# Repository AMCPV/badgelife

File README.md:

#badgelife
==========

Contains hardware CAD files for ec0's various badge mods.

Uses the SAO or LSAO conference badge addon ports. Planning on some SAO v1.69bis add-ons soon!

See Also
--------

- [Resources for #badgelife](https://github.com/devec0/badgelife-parts)

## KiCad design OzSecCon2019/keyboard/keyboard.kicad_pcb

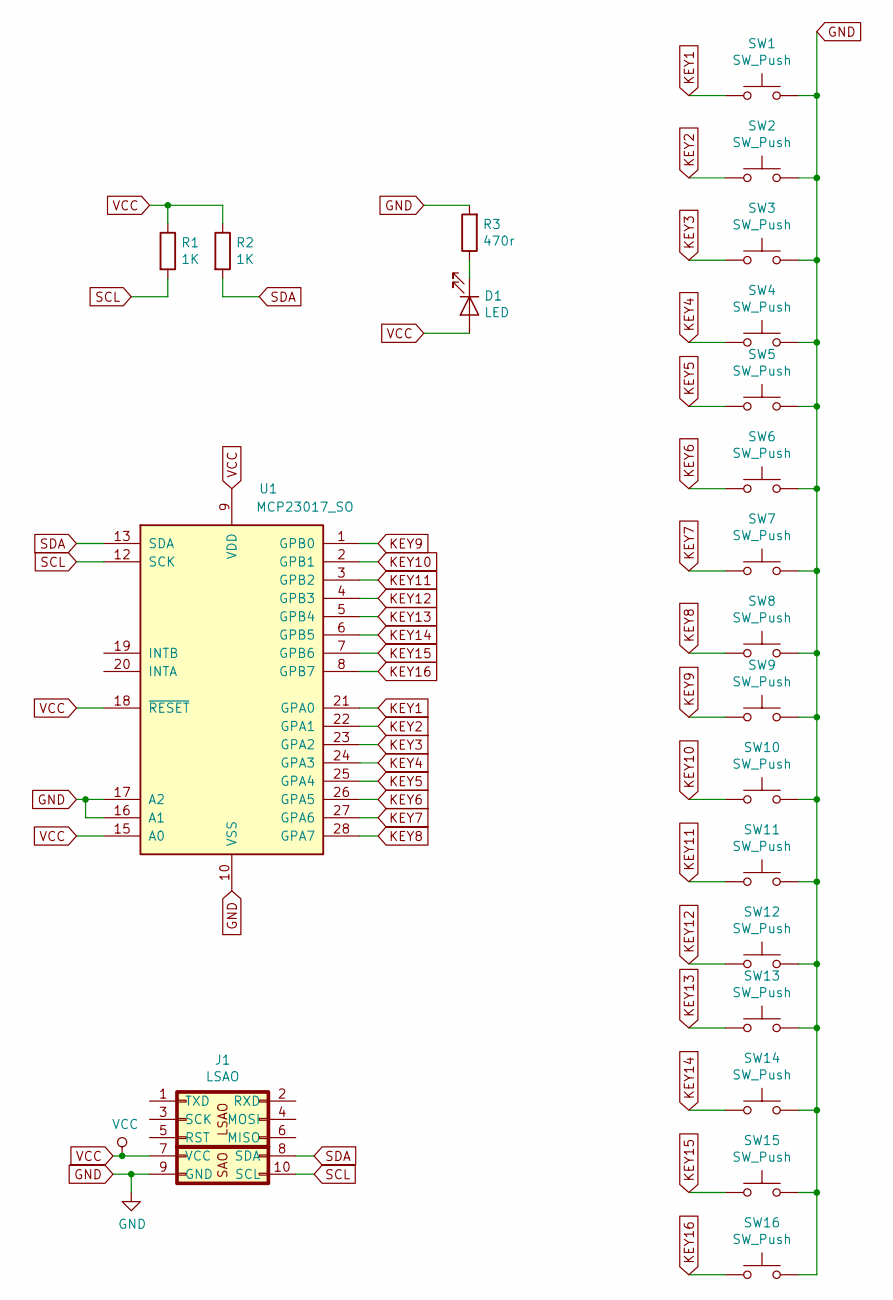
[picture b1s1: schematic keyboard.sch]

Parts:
D1: LED; LED_0805_2012Metric
J1: LSAO; PinSocket_2x05_P2.54mm_Vertical\",
R1, R2: 1K; R_0805_2012Metric
R3: 470r; R_0805_2012Metric
SW1, SW2, SW3, SW4, SW5, SW6, SW7, SW8, SW9, SW10, SW11, SW12, SW13, SW14, SW15, SW16: SW_Push; SW_Cherry_MX1A_1.00u_PCB
U1: MCP23017_SO; SOIC-28W_7.5x17.9mm_P1.27mm

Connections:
GND: J1.9 (GND), R3.2, SW1.2, SW2.2, SW3.2, SW4.2, SW5.2, SW6.2, SW7.2, SW8.2, SW9.2, SW10.2, SW11.2, SW12.2, SW13.2, SW14.2, SW15.2, SW16.2, U1.10 (VSS), U1.16 (A1), U1.17 (A2)
KEY1: SW1.1, U1.21 (GPA0)
KEY2: SW2.1, U1.22 (GPA1)
KEY3: SW3.1, U1.23 (GPA2)
KEY4: SW4.1, U1.24 (GPA3)
KEY5: SW5.1, U1.25 (GPA4)
KEY6: SW6.1, U1.26 (GPA5)
KEY7: SW7.1, U1.27 (GPA6)
KEY8: SW8.1, U1.28 (GPA7)
KEY9: SW9.1, U1.1 (GPB0)
KEY10: SW10.1, U1.2 (GPB1)
KEY11: SW11.1, U1.3 (GPB2)
KEY12: SW12.1, U1.4 (GPB3)
KEY13: SW13.1, U1.5 (GPB4)
KEY14: SW14.1, U1.6 (GPB5)
KEY15: SW15.1, U1.7 (GPB6)
KEY16: SW16.1, U1.8 (GPB7)
unnamed: D1.1 (K), R3.1
SCL: J1.10 (SCL), R1.2, U1.12 (SCK)
SDA: J1.8 (SDA), R2.2, U1.13 (SDA)
VCC: D1.2 (A), J1.7 (VCC), R1.1, R2.1, U1.9 (VDD), U1.15 (A0), U1.18 (~RESET~)

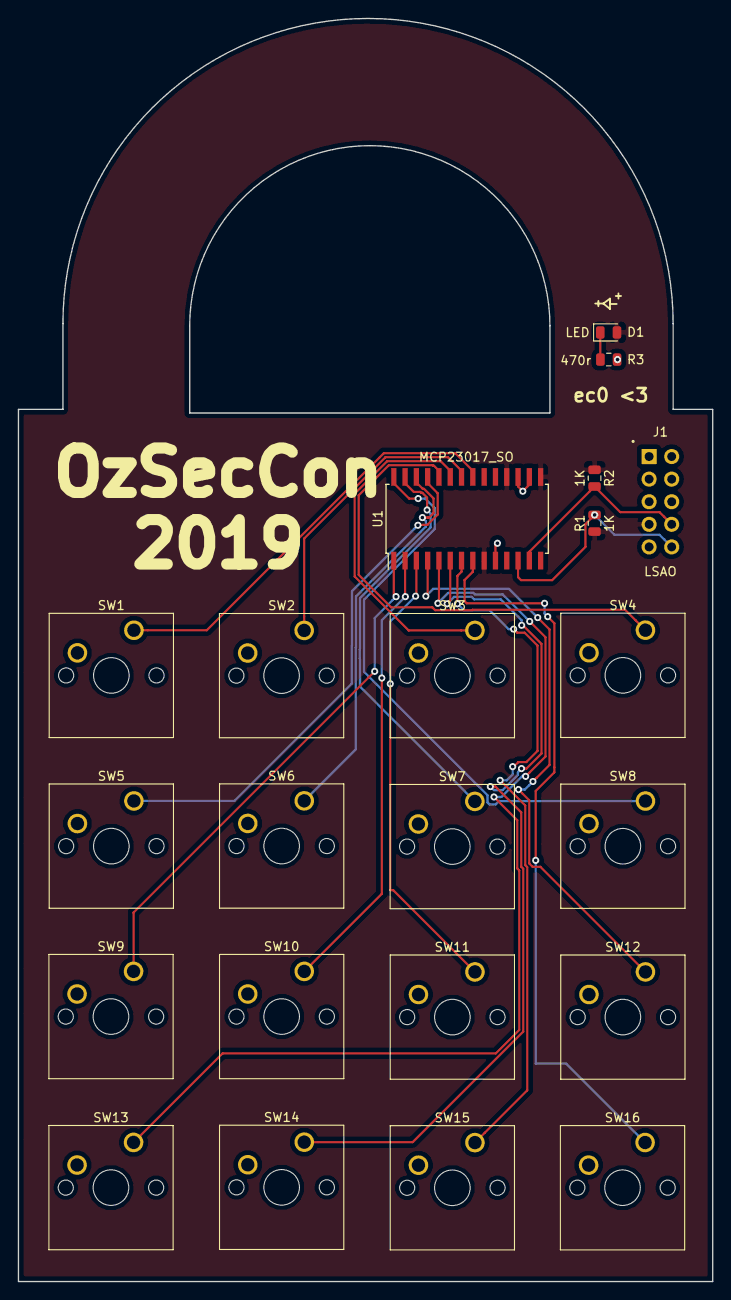
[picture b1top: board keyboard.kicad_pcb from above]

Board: 2 copper layers, 78.0 x 142.0 mm, 22 parts (1 on the bottom side), 21 nets.

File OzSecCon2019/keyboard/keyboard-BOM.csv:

"Id";"Designator";"Package";"Quantity";"Designation";"Supplier and ref";
1;"J1";"PinSocket_2x05_P2.54mm_Vertical";1;"LSAO";;;
2;"R1,R2";"R_0805_2012Metric";2;"1K";;;
3;"SW1,SW2,SW3,SW4,SW5,SW6,SW7,SW8,SW9,SW10,SW11,SW12,SW13,SW14,SW15,SW16";"SW_Cherry_MX1A_1.00u_PCB";16;"SW_Push";;;
4;"U1";"SOIC-28W_7.5x17.9mm_P1.27mm";1;"MCP23017_SO";;;
5;"R3";"R_0805_2012Metric";1;"470r";;;
6;"D1";"LED_0805_2012Metric";1;"LED";;;

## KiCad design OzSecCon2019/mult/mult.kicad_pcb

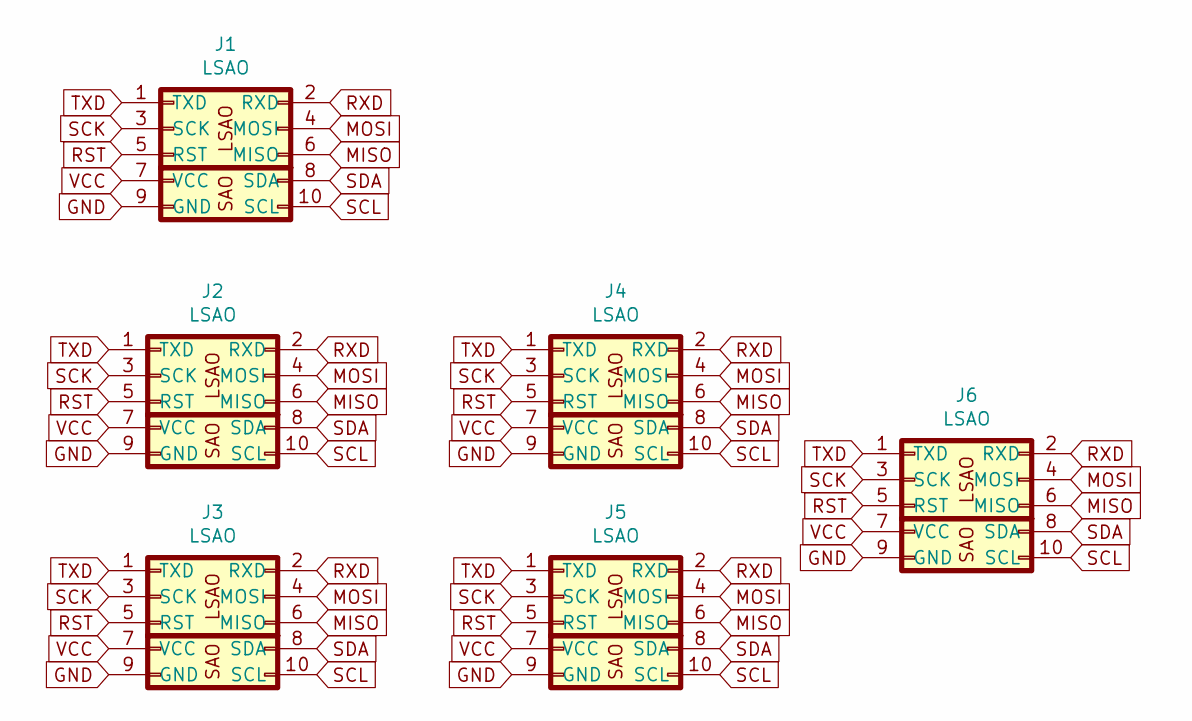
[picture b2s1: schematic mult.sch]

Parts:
J1: LSAO; PinSocket_2x05_P2.54mm_Vertical
J2, J3, J4, J5, J6: LSAO; PinHeader_2x05_P2.54mm_Vertical

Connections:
GND: J1.9 (GND), J2.9 (GND), J3.9 (GND), J4.9 (GND), J5.9 (GND), J6.9 (GND)
MISO: J1.6 (MISO), J2.6 (MISO), J3.6 (MISO), J4.6 (MISO), J5.6 (MISO), J6.6 (MISO)
MOSI: J1.4 (MOSI), J2.4 (MOSI), J3.4 (MOSI), J4.4 (MOSI), J5.4 (MOSI), J6.4 (MOSI)
RST: J1.5 (RST), J2.5 (RST), J3.5 (RST), J4.5 (RST), J5.5 (RST), J6.5 (RST)
RXD: J1.2 (RXD), J2.2 (RXD), J3.2 (RXD), J4.2 (RXD), J5.2 (RXD), J6.2 (RXD)
SCK: J1.3 (SCK), J2.3 (SCK), J3.3 (SCK), J4.3 (SCK), J5.3 (SCK), J6.3 (SCK)
SCL: J1.10 (SCL), J2.10 (SCL), J3.10 (SCL), J4.10 (SCL), J5.10 (SCL), J6.10 (SCL)
SDA: J1.8 (SDA), J2.8 (SDA), J3.8 (SDA), J4.8 (SDA), J5.8 (SDA), J6.8 (SDA)
TXD: J1.1 (TXD), J2.1 (TXD), J3.1 (TXD), J4.1 (TXD), J5.1 (TXD), J6.1 (TXD)
VCC: J1.7 (VCC), J2.7 (VCC), J3.7 (VCC), J4.7 (VCC), J5.7 (VCC), J6.7 (VCC)

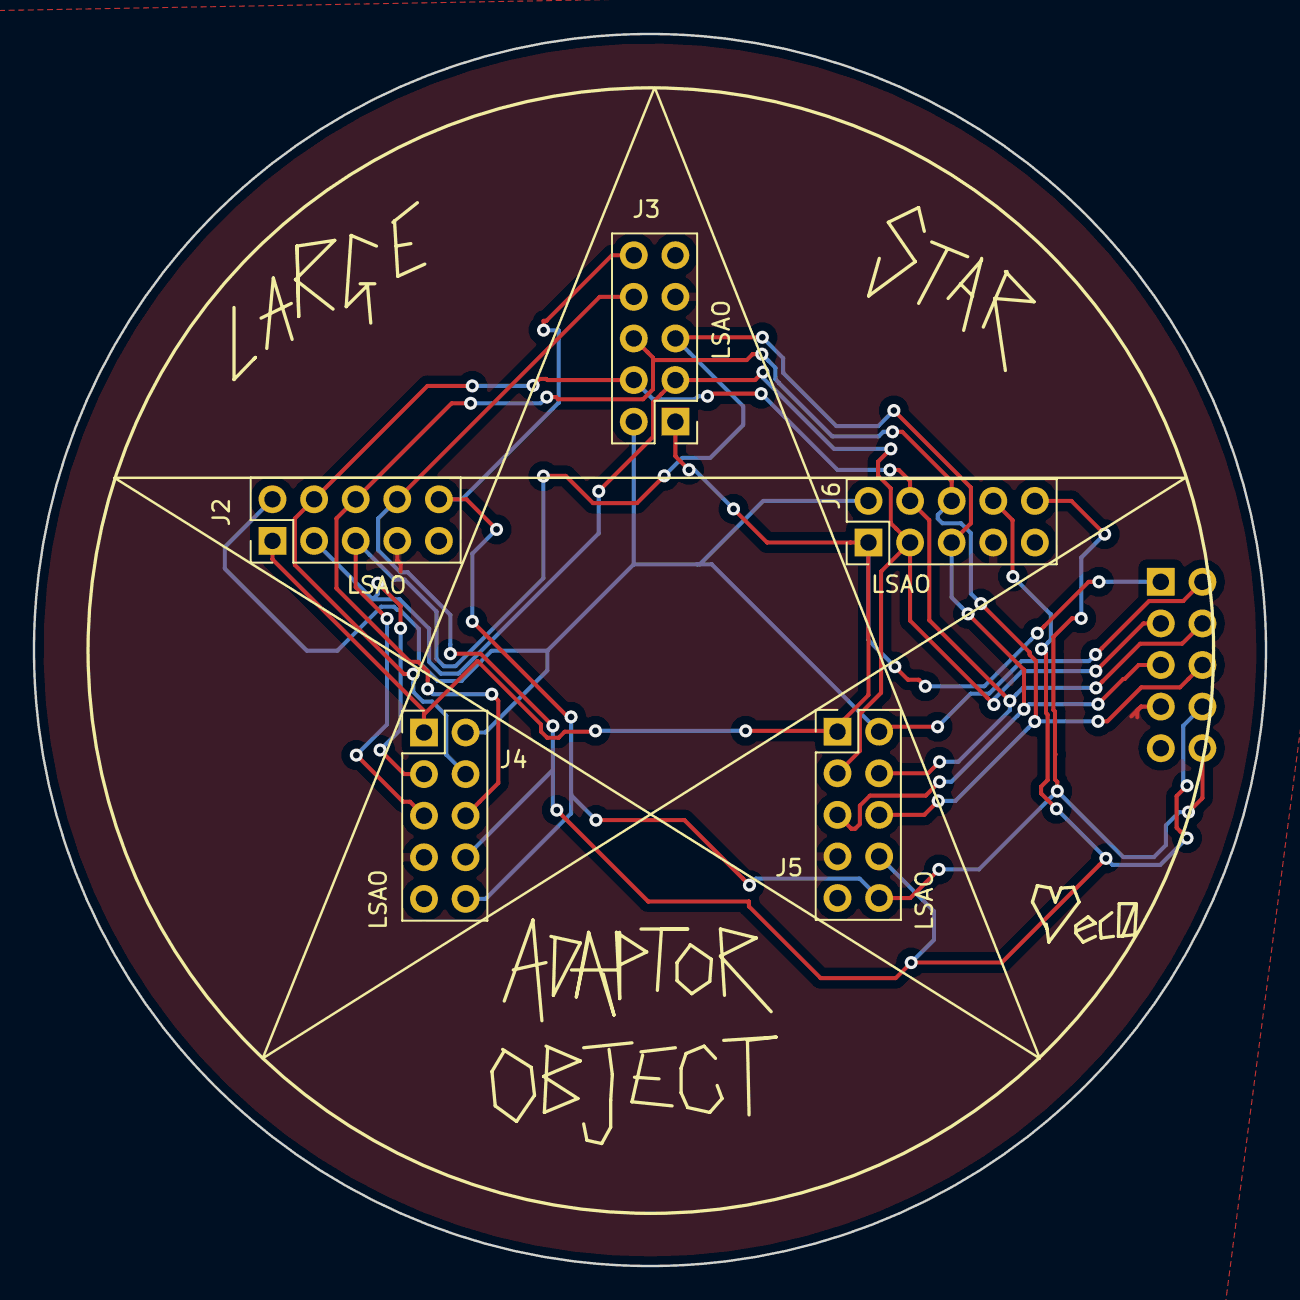
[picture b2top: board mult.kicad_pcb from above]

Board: 2 copper layers, 75.2 x 75.2 mm, 6 parts (1 on the bottom side), 10 nets.

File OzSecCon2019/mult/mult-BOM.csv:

"Id";"Designator";"Package";"Quantity";"Designation";"Supplier and ref";
1;"J1";"PinSocket_2x05_P2.54mm_Vertical";1;"LSAO";;;
2;"J2,J3,J4,J5,J6";"PinHeader_2x05_P2.54mm_Vertical";5;"LSAO";;;

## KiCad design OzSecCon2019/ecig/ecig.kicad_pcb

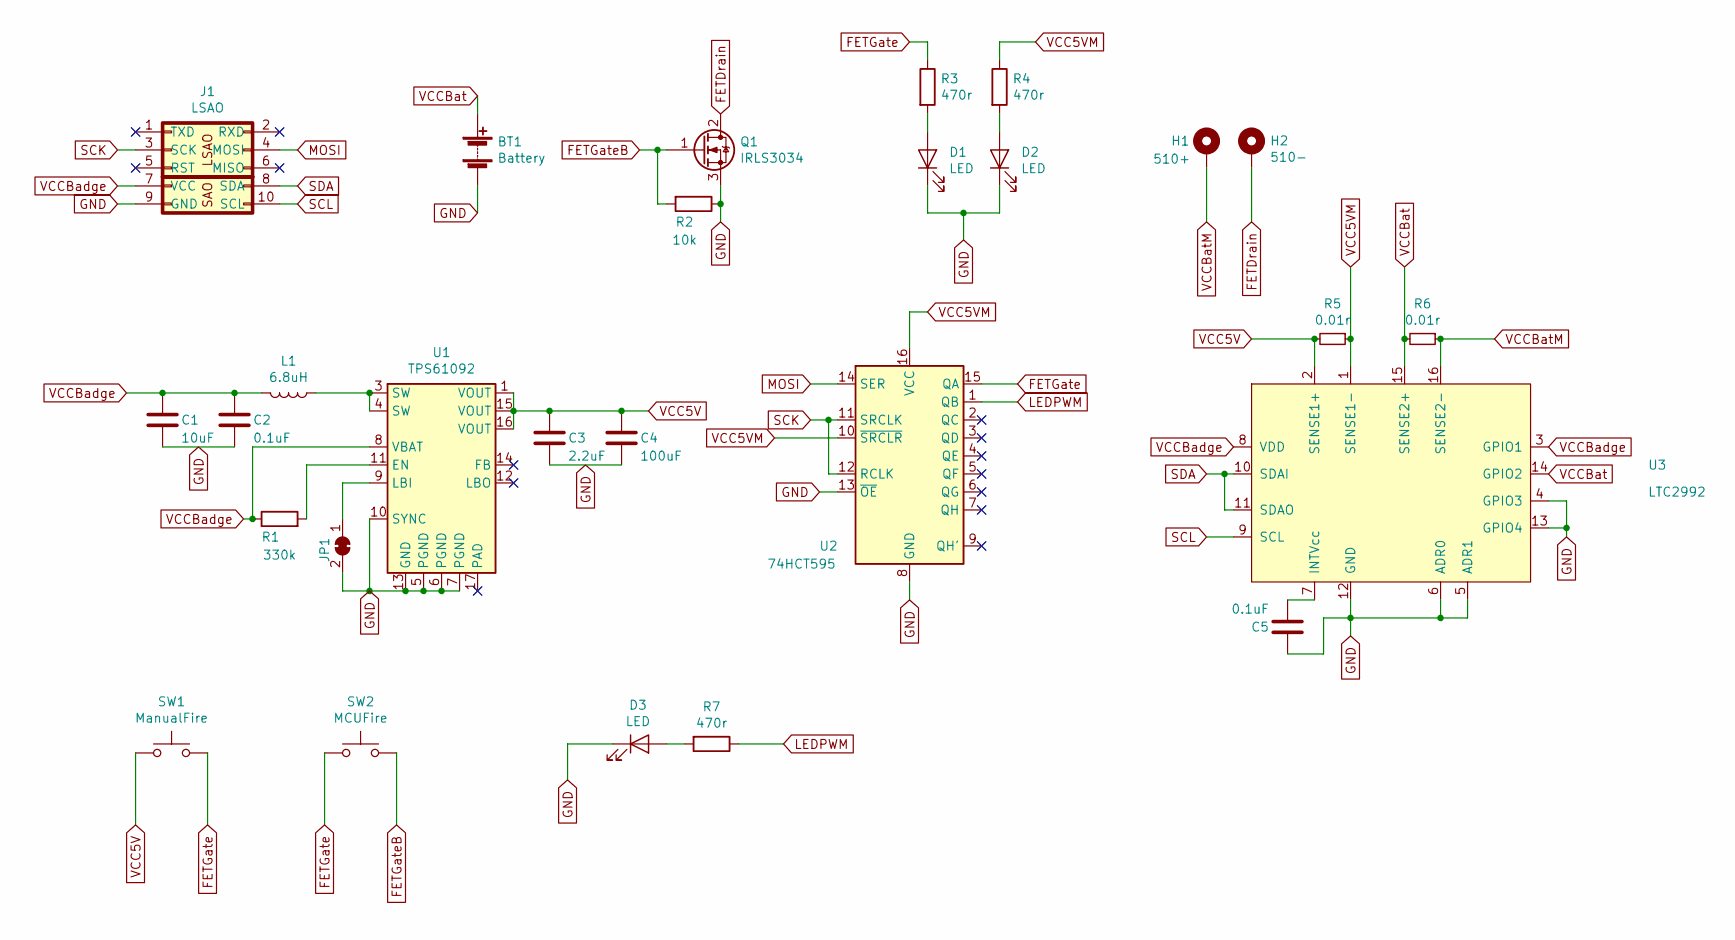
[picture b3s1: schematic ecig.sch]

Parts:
BT1: Battery; BatteryHolder_Keystone_1042_1x18650
C1: 10uF; C_0805_2012Metric
C2, C5: 0.1uF; C_0805_2012Metric
C3: 2.2uF; C_0805_2012Metric
C4: 100uF; C_0805_2012Metric
D1, D2, D3: LED; LED_0805_2012Metric
H1: 510+; Pin_D1.3mm_L11.3mm_W2.8mm_Flat
H2: 510-; Pin_D1.3mm_L11.0mm
J1: LSAO; PinSocket_2x05_P2.54mm_Vertical
JP1: Jumper; SolderJumper-2_P1.3mm_Bridged_RoundedPad1.0x1.5mm
L1: 6.8uH; L_Bourns_SRN6045TA
Q1: IRLS3034; TO-263-3_TabPin2
R1: 330k; R_0805_2012Metric
R2: 10k; R_0805_2012Metric
R3, R4, R7: 470r; R_0805_2012Metric
R5, R6: 0.01r; R_0805_2012Metric
SW1: ManualFire; SW_PUSH_6mm
SW2: MCUFire; SW_PUSH_6mm
U1: TPS61092; QFN-16-1EP_4x4mm_P0.65mm_EP2.5x2.5mm
U2: 74HCT595; SOIC-16_3.9x9.9mm_P1.27mm
U3: LTC2992; MSOP-16_3x4mm_P0.5mm

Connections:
FETDrain: H2.1, Q1.2 (D)
FETGate: R3.1, SW1.2, SW2.1, U2.15 (QA)
FETGateB: Q1.1 (G), R2.2, SW2.2
GND: BT1.2 (-), C1.2, C2.2, C3.2, C4.2, C5.1, D1.1 (K), D2.1 (K), D3.1 (K), J1.9 (GND), JP1.2 (B), Q1.3 (S), R2.1, U1.5 (PGND), U1.6 (PGND), U1.7 (PGND), U1.10 (SYNC), U1.13 (GND), U2.8 (GND), U2.13 (~OE), U3.4 (GPIO3), U3.5 (ADR1), U3.6 (ADR0), U3.12 (GND), U3.13 (GPIO4)
LEDPWM: R7.1, U2.1 (QB)
MOSI: J1.4 (MOSI), U2.14 (SER)
unnamed: C5.2, U3.7 (INTVcc)
unnamed: D1.2 (A), R3.2
unnamed: D2.2 (A), R4.2
unnamed: D3.2 (A), R7.2
unnamed: JP1.1 (A), U1.9 (LBI)
unnamed: L1.1, U1.3 (SW), U1.4 (SW)
unnamed: R1.2, U1.11 (EN)
SCK: J1.3 (SCK), U2.11 (SRCLK), U2.12 (RCLK)
SCL: J1.10 (SCL), U3.9 (SCL)
SDA: J1.8 (SDA), U3.10 (SDAI), U3.11 (SDAO)
VCC5V: C3.1, C4.1, R5.2, SW1.1, U1.1 (VOUT), U1.15 (VOUT), U1.16 (VOUT), U3.2 (SENSE1+)
VCC5VM: R4.1, R5.1, U2.10 (~SRCLR), U2.16 (VCC), U3.1 (SENSE1-)
VCCBadge: C1.1, C2.1, J1.7 (VCC), L1.2, R1.1, U1.8 (VBAT), U3.3 (GPIO1), U3.8 (VDD)
VCCBat: BT1.1 (+), R6.2, U3.14 (GPIO2), U3.15 (SENSE2+)
VCCBatM: H1.1, R6.1, U3.16 (SENSE2-)

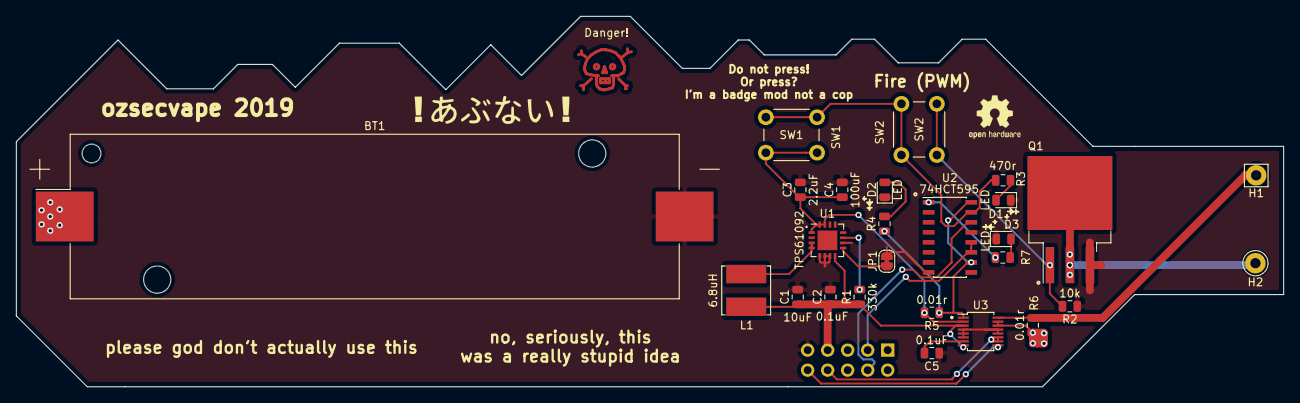
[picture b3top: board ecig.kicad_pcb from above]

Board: 2 copper layers, 160.8 x 47.0 mm, 28 parts (1 on the bottom side), 21 nets.

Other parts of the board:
Danger!: Symbol_Danger_CopperTop_Small

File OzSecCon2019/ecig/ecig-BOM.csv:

"Id";"Designator";"Package";"Quantity";"Designation";"Supplier and ref";
1;"G***";"LOGO";1;"ABUNAI";;;
2;"BT1";"BatteryHolder_Keystone_1042_1x18650";1;"Battery";;;
3;"C1";"C_0805_2012Metric";1;"10uF";;;
4;"C2,C5";"C_0805_2012Metric";2;"0.1uF";;;
5;"C3";"C_0805_2012Metric";1;"2.2uF";;;
6;"C4";"C_0805_2012Metric";1;"100uF";;;
7;"D1,D2,D3";"LED_0805_2012Metric";3;"LED";;;
8;"H1";"Pin_D1.3mm_L11.3mm_W2.8mm_Flat";1;"510+";;;
9;"H2";"Pin_D1.3mm_L11.0mm";1;"510-";;;
10;"J1";"PinSocket_2x05_P2.54mm_Vertical";1;"LSAO";;;
11;"JP1";"SolderJumper-2_P1.3mm_Bridged_RoundedPad1.0x1.5mm";1;"Jumper";;;
12;"L1";"L_Bourns_SRN6045TA";1;"6.8uH";;;
13;"Q1";"TO-263-3_TabPin2";1;"IRLS3034";;;
14;"R1";"R_0805_2012Metric";1;"330k";;;
15;"R2";"R_0805_2012Metric";1;"10k";;;
16;"R3,R4,R7";"R_0805_2012Metric";3;"470r";;;
17;"R5,R6";"R_0805_2012Metric";2;"0.01r";;;
18;"SW1";"SW_PUSH_6mm";1;"ManualFire";;;
19;"SW2";"SW_PUSH_6mm";1;"MCUFire";;;
20;"U1";"QFN-16-1EP_4x4mm_P0.65mm_EP2.5x2.5mm";1;"TPS61092";;;
21;"U2";"SOIC-16_3.9x9.9mm_P1.27mm";1;"74HCT595";;;
22;"U3";"MSOP-16_3x4mm_P0.5mm";1;"LTC2992";;;
23;"REF**";"OSHW-Logo2_7.3x6mm_SilkScreen";1;"OSHW-Logo2_7.3x6mm_SilkScreen";;;
24;"Danger!";"Symbol_Danger_CopperTop_Small";1;"Symbol_Danger_CopperTop_Small";;;

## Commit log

2019-06-21 Added badge addons from OzSecCon2019
